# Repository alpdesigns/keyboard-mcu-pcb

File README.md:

# keyboard-mcu-pcb

## About

A keyboard MCU PCB that can be connected with the key matrix PCB with a FFC cable. Designed for simplifying routing and removing MLC capacitors from the matrix PCB.

## Features

- Open Source.
- ESD protection diodes.
- Compatible with a 30 pins, 0.5 mm pitch FFC.

## Dimensions

- All holes are M2 clearance hole.
- All corner radii are 2.5 mm.
- PCB thickness is 1.6 mm.

## FFC Wiring

| pins               | usage                    |
|:-------------------|:-------------------------|
| 1-2                | Vcc                      |
| 3                  | RGBLED (PWM enabled pin) |
| 4                  | GND                      |
| 5-8                | Interrupt Pins           |
| 9-12, 14-21, 23-24 | 14 Cols                  |
| 25-30              | 6 Rows                   |

## License

MIT otherwise noted.

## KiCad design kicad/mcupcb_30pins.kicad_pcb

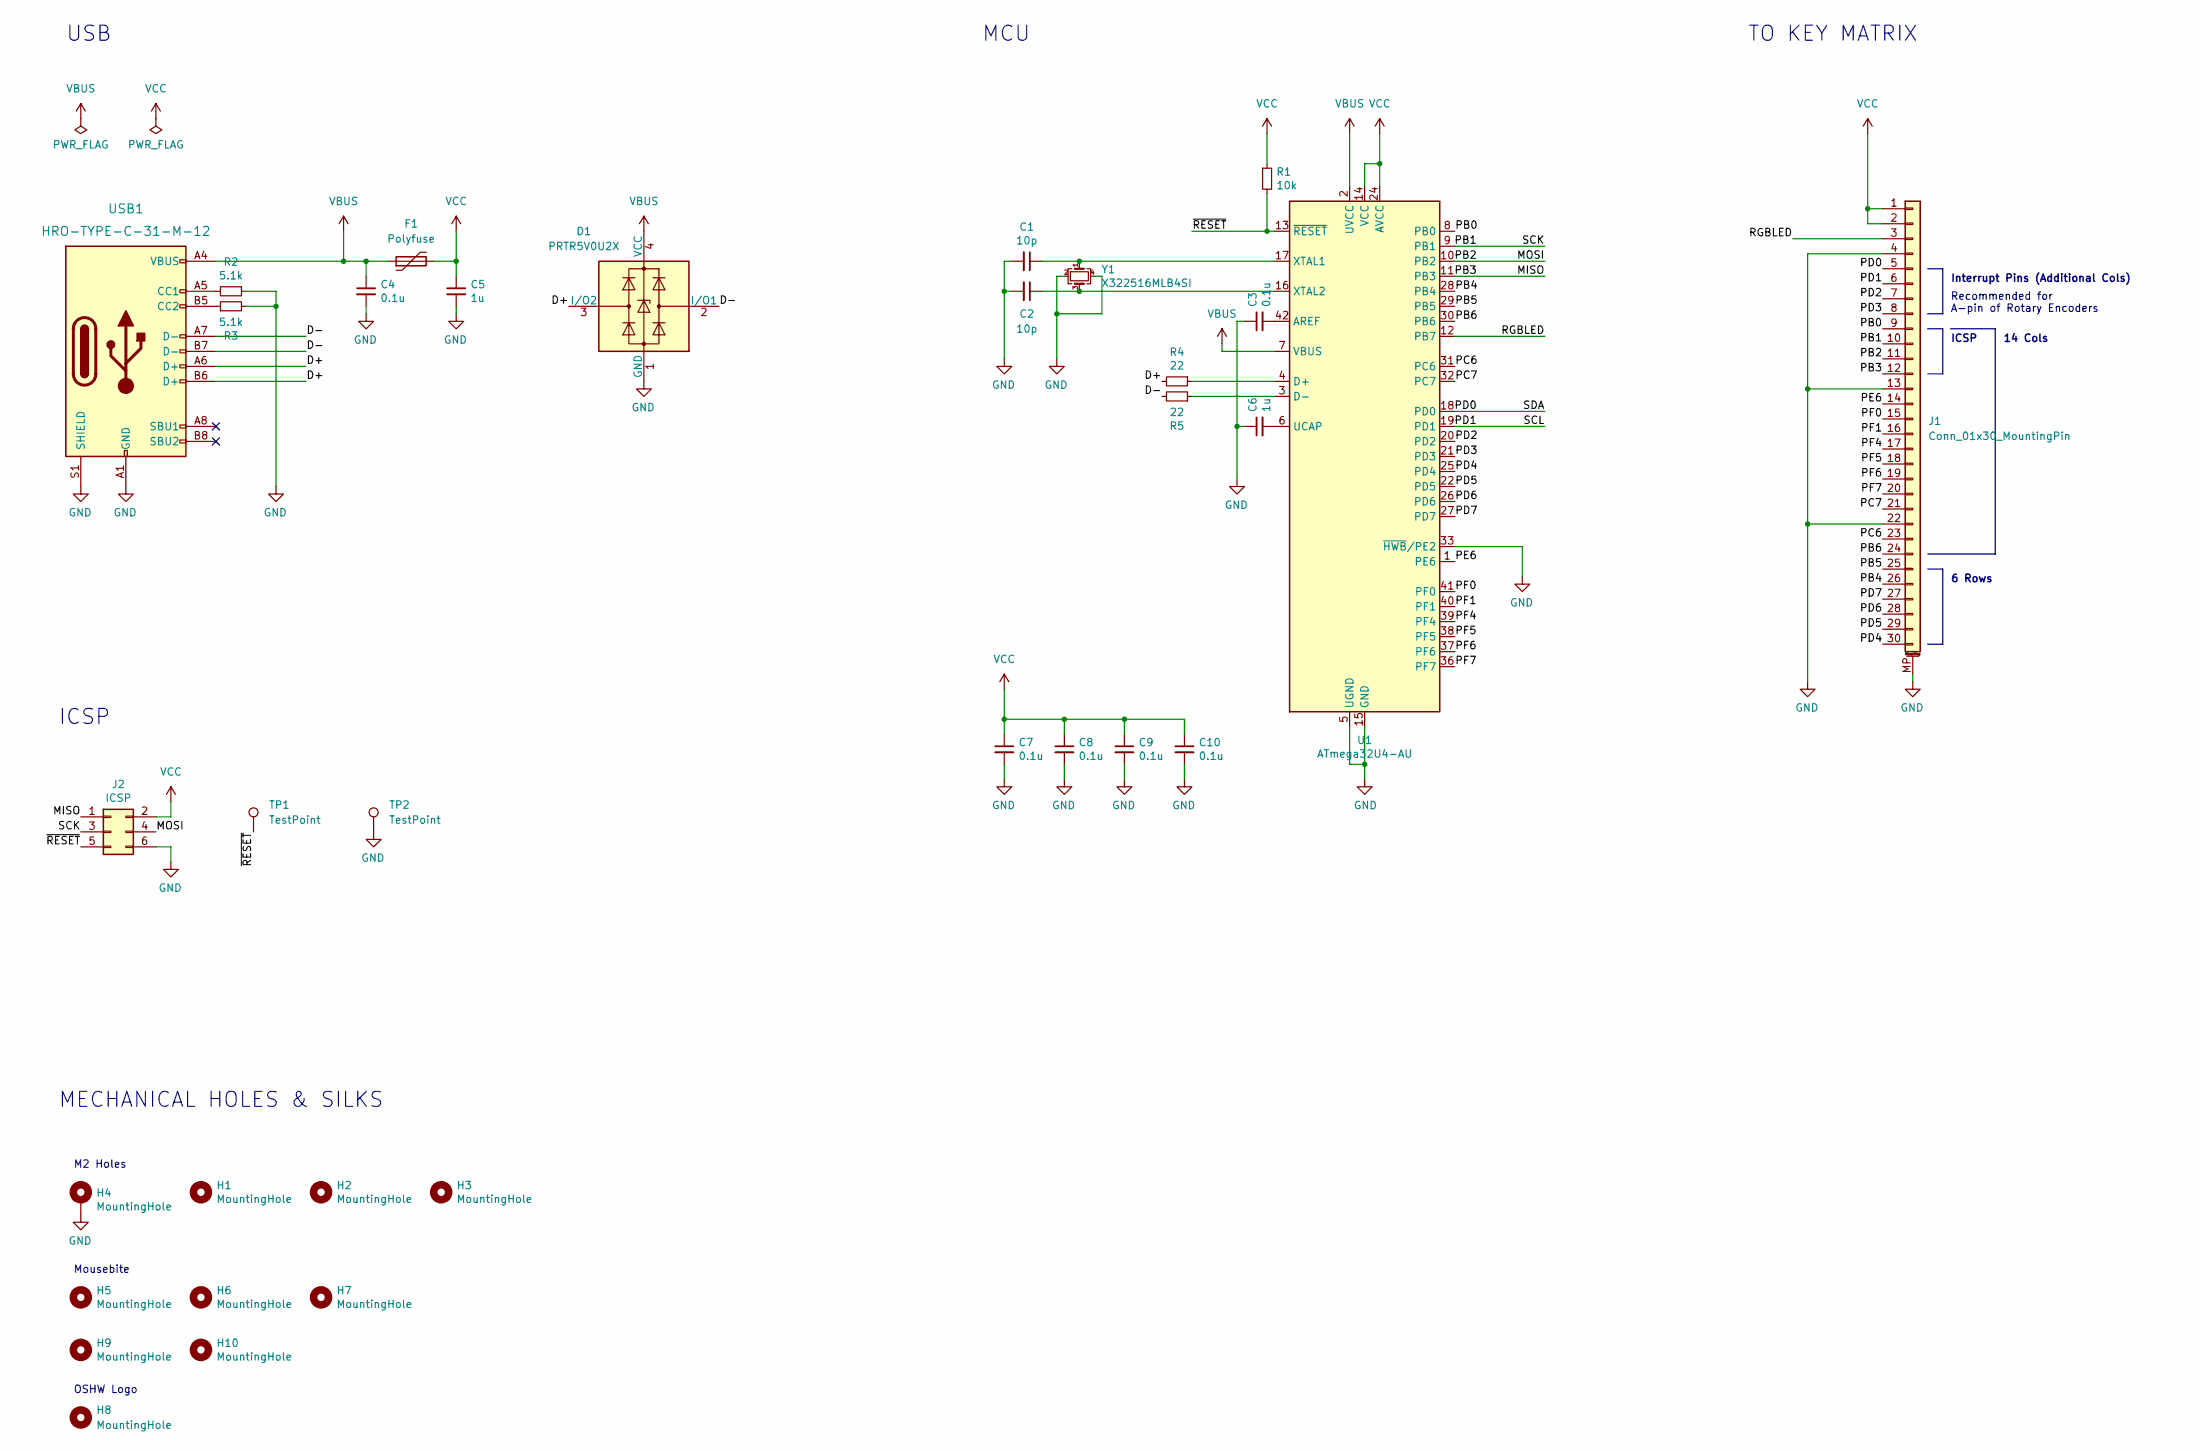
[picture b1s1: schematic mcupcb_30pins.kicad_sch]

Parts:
C1, C2: 10p; C_0603_1608Metric; LCSC C1634
C3, C4, C7, C8, C9, C10: 0.1u; C_0603_1608Metric; LCSC C14663
C5, C6: 1u; C_0805_2012Metric; LCSC C28323
D1: PRTR5V0U2X; SOT-143; LCSC C12333
F1: Polyfuse; Fuse_1206_3216Metric; LCSC C151162
H1, H2, H3: MountingHole; MountingHole_M2_NoCu; LCSC N/A
H4: MountingHole; MountingHole_M2_PTH; LCSC N/A
H5, H6, H7: MountingHole; Breakaway_small; LCSC N/A
H8: MountingHole; OSHW-Logo_5.7x6mm_SilkScreen; LCSC N/A
H9, H10: MountingHole; Breakaway_panel; LCSC N/A
J1: Conn_01x30_MountingPin; Hirose_FH12-30S-0.5SH_1x30-1MP_P0.50mm_Horizontal; LCSC C506793
J2: ICSP; Tag-Connect_TC2030-IDC-NL_2x03_P1.27mm_Vertical; LCSC N/A
R1: 10k; R_0603_1608Metric; LCSC C25804
R2, R3: 5.1k; R_0603_1608Metric; LCSC C23186
R4, R5: 22; R_0603_1608Metric; LCSC C23345
TP1, TP2: TestPoint; TestPoint_Pad_D1.5mm; LCSC N/A
U1: ATmega32U4-AU; TQFP-44_10x10mm_P0.8mm; LCSC N/A
USB1: HRO-TYPE-C-31-M-12; USB_C_Receptacle_HRO_TYPE-C-31-M-12; LCSC C165948
Y1: X322516MLB4SI; Crystal_SMD_3225-4Pin_3.2x2.5mm; LCSC C13738

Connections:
/D+: D1.3 (I/O2), R4.2, USB1.A6 (D+), USB1.B6 (D+)
/D-: D1.2 (I/O1), R5.2, USB1.A7 (D-), USB1.B7 (D-)
/MISO: J1.12, J2.1, U1.11 (PB3)
/MOSI: J1.11, J2.4, U1.10 (PB2)
/PB0: J1.9, U1.8 (PB0)
/PB1: J1.10, J2.3, U1.9 (PB1)
/PB4: J1.26, U1.28 (PB4)
/PB5: J1.25, U1.29 (PB5)
/PB6: J1.24, U1.30 (PB6)
/PC6: J1.23, U1.31 (PC6)
/PC7: J1.21, U1.32 (PC7)
/PD0: J1.5, U1.18 (PD0)
/PD1: J1.6, U1.19 (PD1)
/PD2: J1.7, U1.20 (PD2)
/PD3: J1.8, U1.21 (PD3)
/PD4: J1.30, U1.25 (PD4)
/PD5: J1.29, U1.22 (PD5)
/PD6: J1.28, U1.26 (PD6)
/PD7: J1.27, U1.27 (PD7)
/PE6: J1.14, U1.1 (PE6)
/PF0: J1.15, U1.41 (PF0)
/PF1: J1.16, U1.40 (PF1)
/PF4: J1.17, U1.39 (PF4)
/PF5: J1.18, U1.38 (PF5)
/PF6: J1.19, U1.37 (PF6)
/PF7: J1.20, U1.36 (PF7)
/RGBLED: J1.3, U1.12 (PB7)
/~RESET: J2.5, R1.2, TP1.1, U1.13 (~RESET)
GND: C1.2, C2.2, C3.1, C4.2, C5.2, C6.1, C7.2, C8.2, C9.2, C10.2, D1.1 (GND), H4.1, J1.4, J1.13, J1.22, J1.MP (MountPin), J2.6, R2.1, R3.2, TP2.1, U1.5 (UGND), U1.15 (GND), U1.23 (GND), U1.33 (~HWB/PE2), U1.35 (GND), U1.43 (GND), USB1.A1 (GND), USB1.A12 (GND), USB1.B1 (GND), USB1.B12 (GND), USB1.S1 (SHIELD), Y1.2, Y1.4
unnamed: C1.1, U1.17 (XTAL1), Y1.1
unnamed: C2.1, U1.16 (XTAL2), Y1.3
unnamed: C3.2, U1.42 (AREF)
unnamed: C6.2, U1.6 (UCAP)
unnamed: R2.2, USB1.A5 (CC1)
unnamed: R3.1, USB1.B5 (CC2)
unnamed: R4.1, U1.4 (D+)
unnamed: R5.1, U1.3 (D-)
VBUS: C4.1, D1.4 (VCC), F1.1, U1.2 (UVCC), U1.7 (VBUS), USB1.A4 (VBUS), USB1.A9 (VBUS), USB1.B4 (VBUS), USB1.B9 (VBUS)
VCC: C5.1, C7.1, C8.1, C9.1, C10.1, F1.2, J1.1, J1.2, J2.2, R1.1, U1.14 (VCC), U1.24 (AVCC), U1.34 (VCC), U1.44 (AVCC)

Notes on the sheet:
ICSP
USB
Mousebite
Recommended for A-pin of Rotary Encoders
M2 Holes
MECHANICAL HOLES & SILKS
OSHW Logo
MCU
Interrupt Pins (Additional Cols)
6 Rows
14 Cols
TO KEY MATRIX

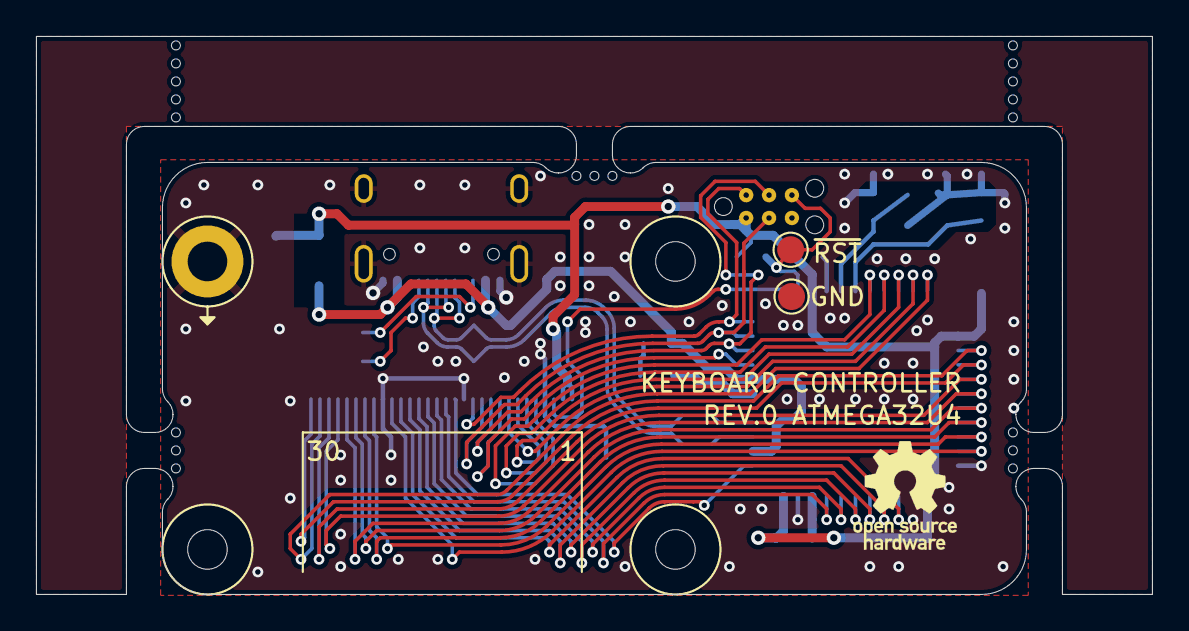
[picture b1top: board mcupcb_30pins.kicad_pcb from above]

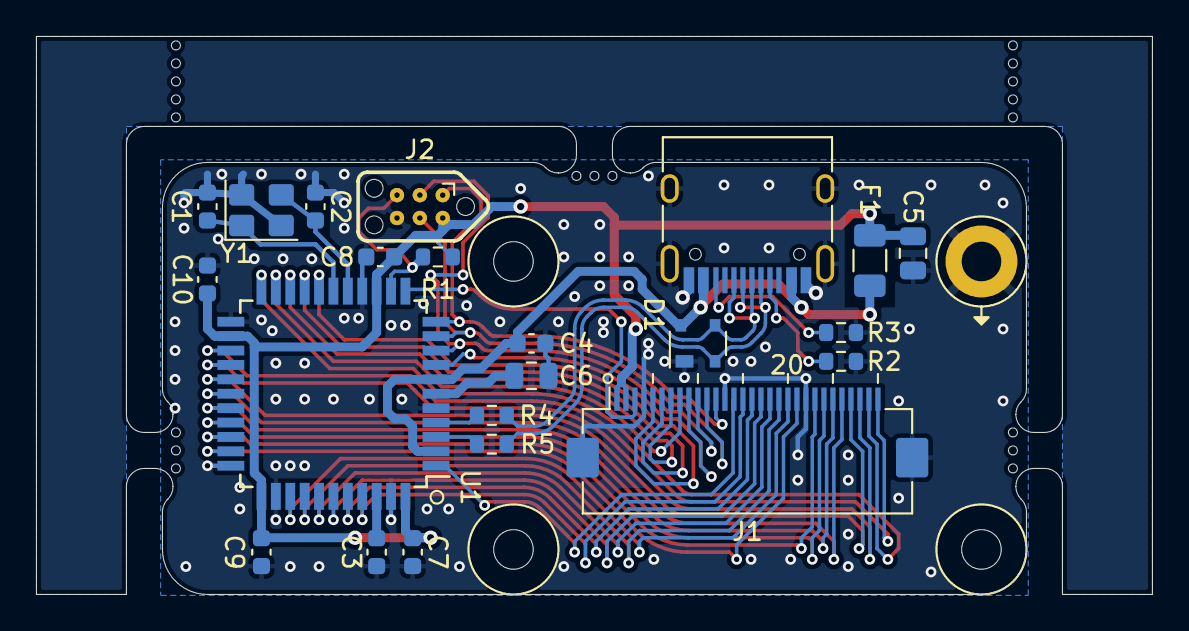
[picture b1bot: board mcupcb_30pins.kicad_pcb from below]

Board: 2 copper layers, 62.0 x 31.0 mm, 34 parts (26 on the bottom side), 39 nets.

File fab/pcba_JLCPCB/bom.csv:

Designator,Comment,Footprint,LCSC
"C1, C2, ",10p,Capacitor_SMD:C_0603_1608Metric,C1634
"C3, C4, C7, C8, C9, C10, ",0.1u,Capacitor_SMD:C_0603_1608Metric,C14663
"C5, C6, ",1u,Capacitor_SMD:C_0805_2012Metric,C28323
"D1, ",PRTR5V0U2X,Package_TO_SOT_SMD:SOT-143,C12333
"F1, ",Polyfuse,Fuse:Fuse_1206_3216Metric,C151162
"J1, ",Conn_01x30_MountingPin,Connector_FFC-FPC:Hirose_FH12-30S-0.5SH_1x30-1MP_P0.50mm_Horizontal,C506793
"R1, ",10k,Resistor_SMD:R_0603_1608Metric,C25804
"R2, R3, ",5.1k,Resistor_SMD:R_0603_1608Metric,C23186
"R4, R5, ",22,Resistor_SMD:R_0603_1608Metric,C23345
"USB1, ",HRO-TYPE-C-31-M-12,USB_C_Receptacle_USB2.0,C165948
"Y1, ",X322516MLB4SI,Crystal:Crystal_SMD_3225-4Pin_3.2x2.5mm,C13738

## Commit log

2022-05-06 Fixed flipped D+/D-
